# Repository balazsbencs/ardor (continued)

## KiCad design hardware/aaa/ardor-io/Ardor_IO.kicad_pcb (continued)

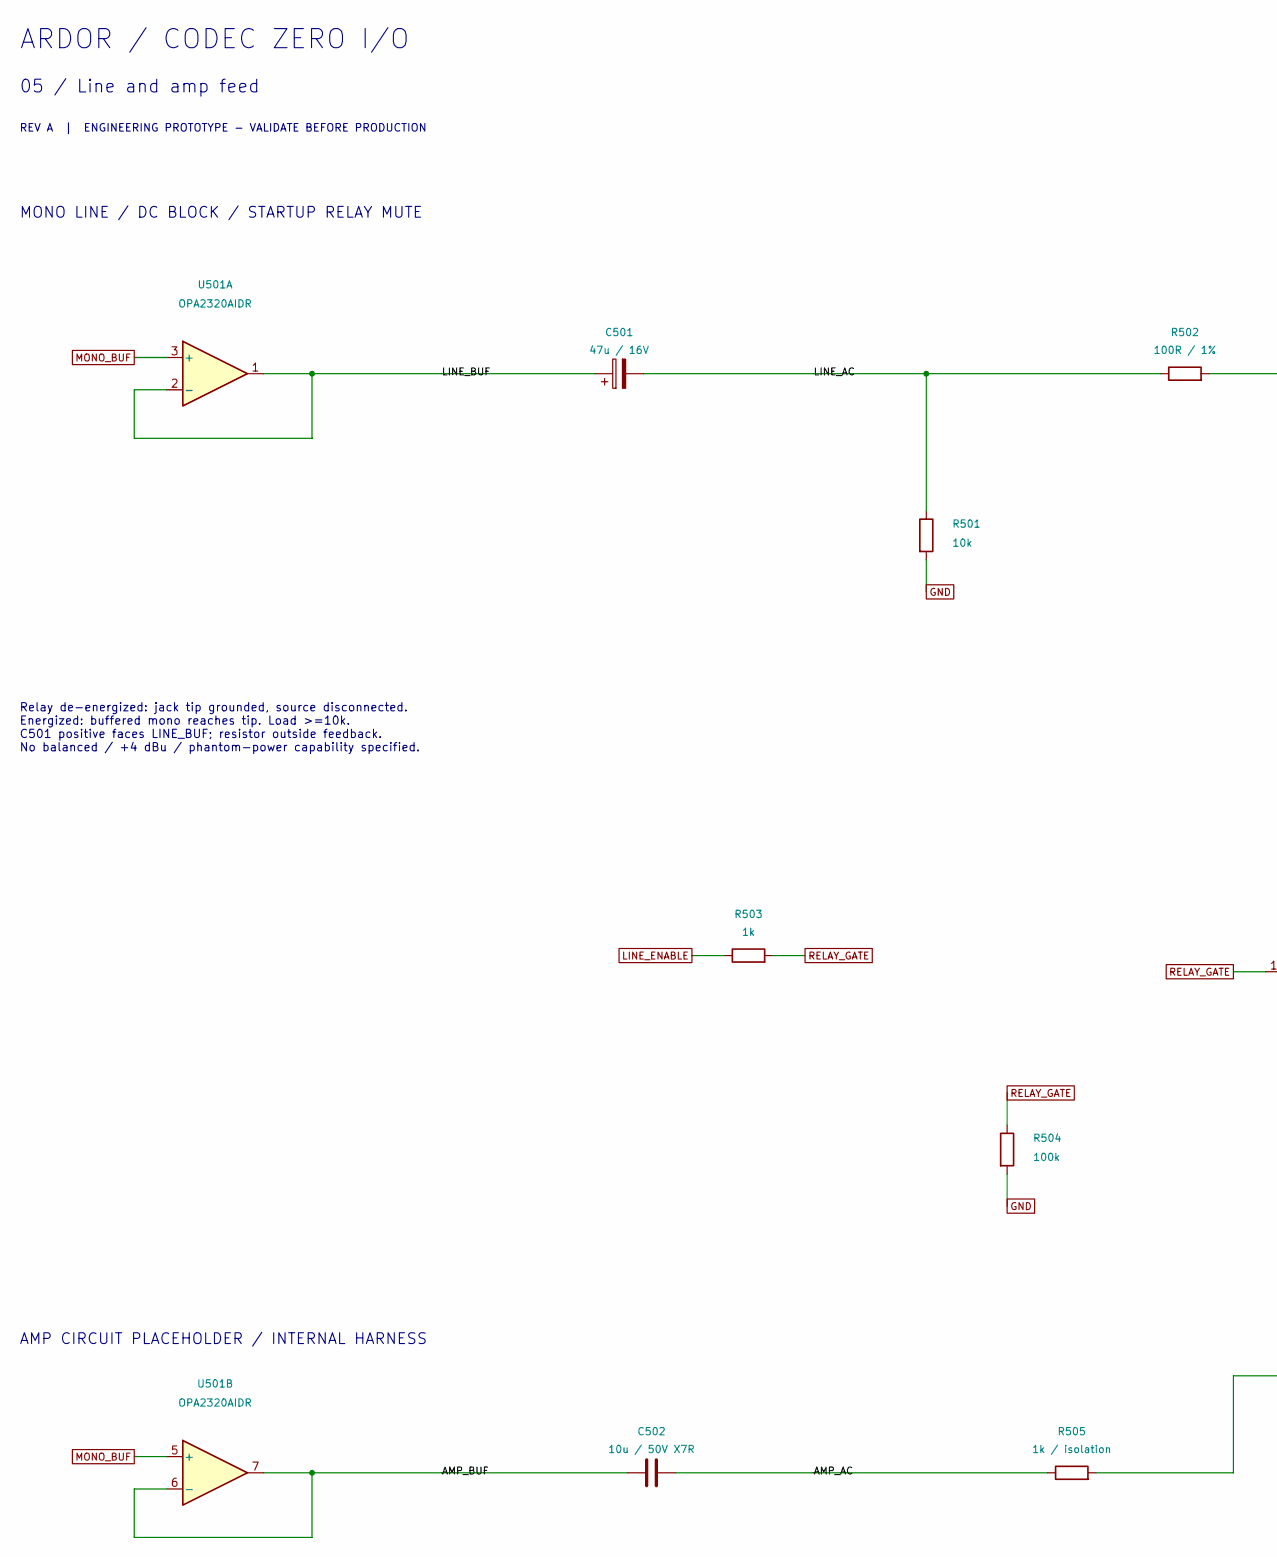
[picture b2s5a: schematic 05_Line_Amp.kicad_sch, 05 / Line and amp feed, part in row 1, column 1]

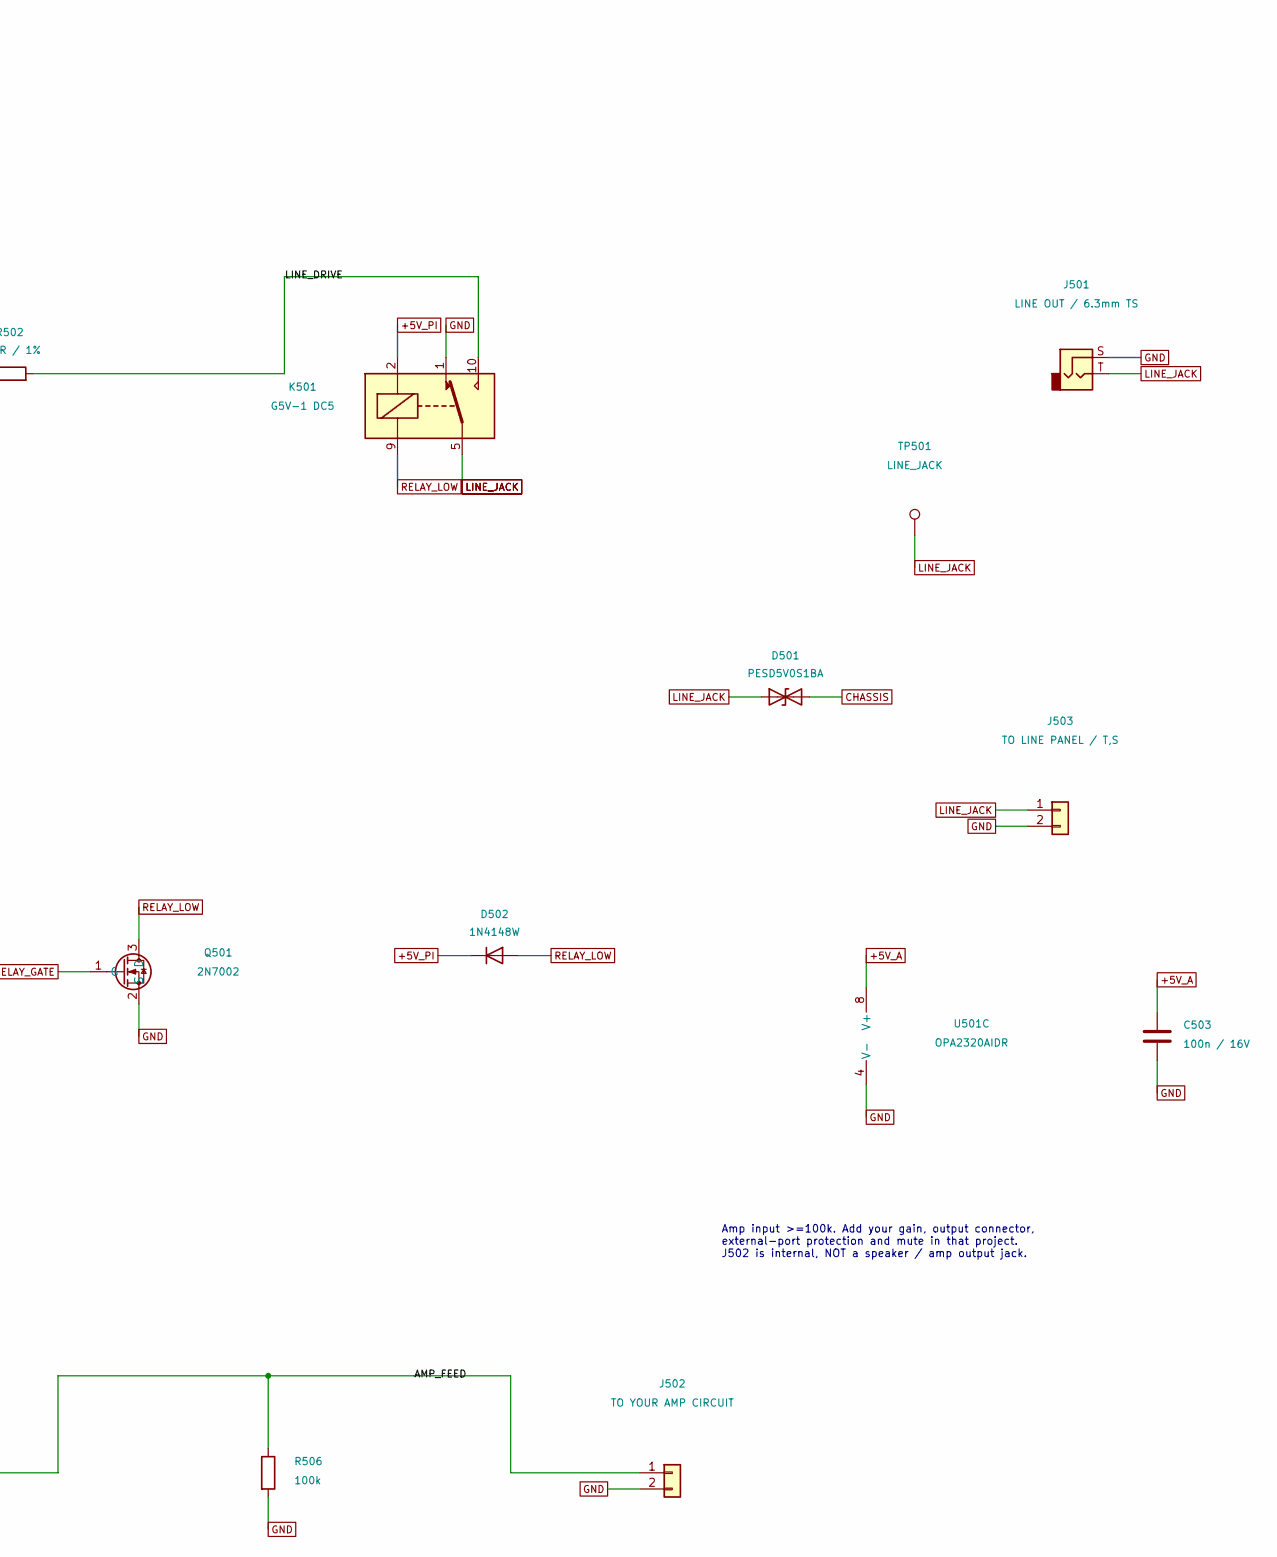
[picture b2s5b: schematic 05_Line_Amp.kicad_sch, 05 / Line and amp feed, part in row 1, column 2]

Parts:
C501: 47u / 16V; CP_Elec_6.3x5.4; MPN Panasonic EEE-FK1C470R
C502: 10u / 50V X7R; C_1206_3216Metric; MPN Samsung CL31B106KBHNNNE; JLCPCB Part # C89632
C503: 100n / 16V; C_0603_1608Metric
D501: PESD5V0S1BA; D_SOD-323; MPN Nexperia PESD5V0S1BA
D502: 1N4148W; D_SOD-123; MPN 1N4148W
J501: LINE OUT / 6.3mm TS
J502: TO YOUR AMP CIRCUIT; PinHeader_1x02_P2.54mm_Vertical
J503: TO LINE PANEL / T,S; PinHeader_1x02_P2.54mm_Vertical
K501: G5V-1 DC5; Relay_SPDT_Omron_G5V-1; MPN Omron G5V-1 DC5
Q501: 2N7002; SOT-23; MPN Nexperia 2N7002
R501: 10k; R_0603_1608Metric
R502: 100R / 1%; R_0603_1608Metric
R503: 1k; R_0603_1608Metric
R504, R506: 100k; R_0603_1608Metric
R505: 1k / isolation; R_0603_1608Metric
TP501: LINE_JACK; TestPoint_Pad_D1.5mm
U501: OPA2320AIDR; SOIC-8_3.9x4.9mm_P1.27mm; MPN TI OPA2320AIDR

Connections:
+5V_A: C503.1, U501.8 (V+); also elsewhere on the board
+5V_PI: D502.1 (K), K501.2; also elsewhere on the board
/05 / Line and amp feed/AMP_AC: C502.2, R505.1
/05 / Line and amp feed/AMP_BUF: C502.1, U501.6 (-), U501.7
/05 / Line and amp feed/AMP_FEED: J502.1, R505.2, R506.1
/05 / Line and amp feed/LINE_AC: C501.2, R501.1, R502.1
/05 / Line and amp feed/LINE_BUF: C501.1, U501.1, U501.2 (-)
/05 / Line and amp feed/LINE_DRIVE: K501.10, R502.2
CHASSIS: D501.2 (A2); also elsewhere on the board
GND: C503.2, J501.S, J502.2, J503.2, K501.1, Q501.2 (S), R501.2, R504.2, R506.2, U501.4 (V-); also elsewhere on the board
LINE_ENABLE: R503.1; also elsewhere on the board
LINE_JACK: D501.1 (A1), J501.T, J503.1, K501.5, K501.6, TP501.1
MONO_BUF: U501.3 (+), U501.5 (+); also elsewhere on the board
RELAY_GATE: Q501.1 (G), R503.2, R504.1
RELAY_LOW: D502.2 (A), K501.9, Q501.3 (D)

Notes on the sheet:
ARDOR / CODEC ZERO I/O
05 / Line and amp feed
REV A | ENGINEERING PROTOTYPE - VALIDATE BEFORE PRODUCTION
MONO LINE / DC BLOCK / STARTUP RELAY MUTE
Relay de-energized: jack tip grounded, source disconnected. Energized: buffered mono reaches tip. Load >=10k. C501 positive faces LINE_BUF; resistor outside feedback. No balanced / +4 dBu / phantom-power capability specified.
AMP CIRCUIT PLACEHOLDER / INTERNAL HARNESS
Amp input >=100k. Add your gain, output connector, external-port protection and mute in that project. J502 is internal, NOT a speaker / amp output jack.

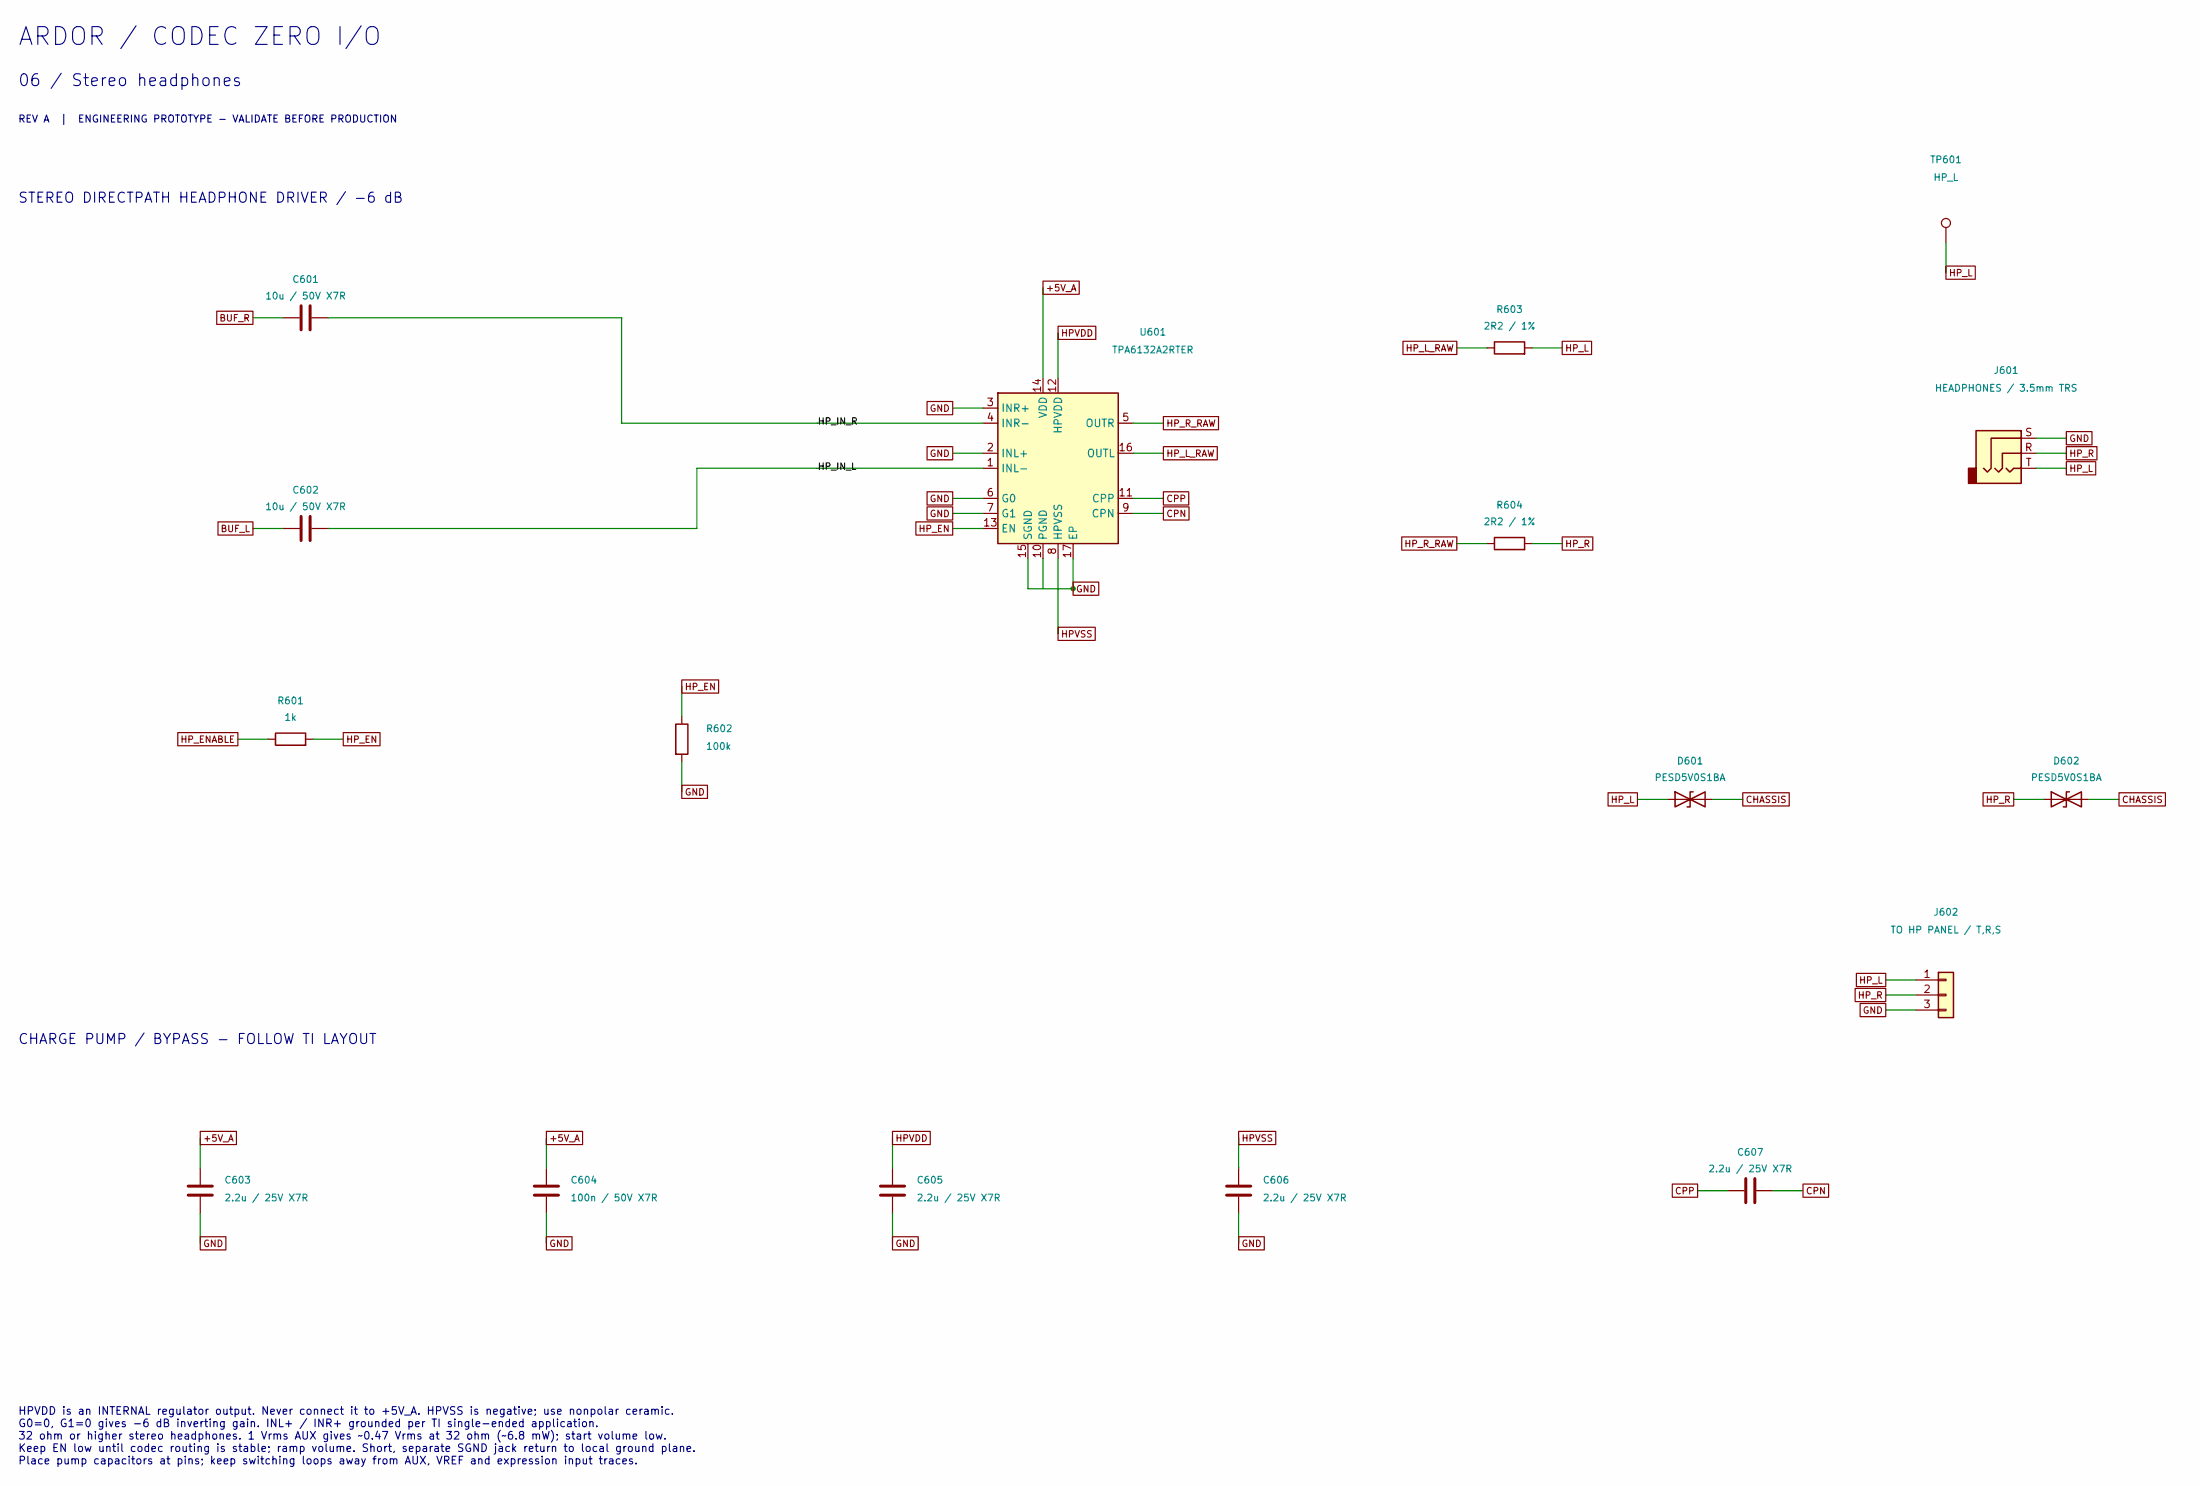
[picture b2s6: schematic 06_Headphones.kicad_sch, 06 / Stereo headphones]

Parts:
C601, C602: 10u / 50V X7R; C_1206_3216Metric; MPN Samsung CL31B106KBHNNNE; JLCPCB Part # C89632
C603, C605, C606, C607: 2.2u / 25V X7R; C_0805_2012Metric; MPN Samsung CL21B225KAFNNNE; JLCPCB Part # C19110
C604: 100n / 50V X7R; C_0603_1608Metric; MPN YAGEO CC0603KRX7R9BB104; JLCPCB Part # C14663
D601, D602: PESD5V0S1BA; D_SOD-323; MPN Nexperia PESD5V0S1BA,115; JLCPCB Part # C19224
J601: HEADPHONES / 3.5mm TRS
J602: TO HP PANEL / T,R,S; PinHeader_1x03_P2.54mm_Vertical
R601: 1k; R_0603_1608Metric; MPN UNI-ROYAL 0603WAF1001T5E; JLCPCB Part # C21190
R602: 100k; R_0603_1608Metric; MPN UNI-ROYAL 0603WAF1003T5E; JLCPCB Part # C25803
R603, R604: 2R2 / 1%; R_0603_1608Metric; MPN UNI-ROYAL 0603WAF220KT5E; JLCPCB Part # C22939
TP601: HP_L; TestPoint_Pad_D1.5mm
U601: TPA6132A2RTER; WQFN-16-1EP_3x3mm_P0.5mm_EP1.6x1.6mm_ThermalVias; MPN TI TPA6132A2RTER; JLCPCB Part # C69901

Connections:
+5V_A: C603.1, C604.1, U601.14 (VDD); also elsewhere on the board
/06 / Stereo headphones/HP_IN_L: C602.2, U601.1 (INL-)
/06 / Stereo headphones/HP_IN_R: C601.2, U601.4 (INR-)
BUF_L: C602.1; also elsewhere on the board
BUF_R: C601.1; also elsewhere on the board
CHASSIS: D601.2 (A2), D602.2 (A2); also elsewhere on the board
CPN: C607.2, U601.9 (CPN)
CPP: C607.1, U601.11 (CPP)
GND: C603.2, C604.2, C605.2, C606.2, J601.S, J602.3, R602.2, U601.2 (INL+), U601.3 (INR+), U601.6 (G0), U601.7 (G1), U601.10 (PGND), U601.15 (SGND), U601.17 (EP); also elsewhere on the board
HPVDD: C605.1, U601.12 (HPVDD)
HPVSS: C606.1, U601.8 (HPVSS)
HP_EN: R601.2, R602.1, U601.13 (EN)
HP_ENABLE: R601.1; also elsewhere on the board
HP_L: D601.1 (A1), J601.T, J602.1, R603.2, TP601.1
HP_L_RAW: R603.1, U601.16 (OUTL)
HP_R: D602.1 (A1), J601.R, J602.2, R604.2
HP_R_RAW: R604.1, U601.5 (OUTR)

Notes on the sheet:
ARDOR / CODEC ZERO I/O
06 / Stereo headphones
REV A | ENGINEERING PROTOTYPE - VALIDATE BEFORE PRODUCTION
STEREO DIRECTPATH HEADPHONE DRIVER / -6 dB
CHARGE PUMP / BYPASS - FOLLOW TI LAYOUT
HPVDD is an INTERNAL regulator output. Never connect it to +5V_A. HPVSS is negative; use nonpolar ceramic. G0=0, G1=0 gives -6 dB inverting gain. INL+ / INR+ grounded per TI single-ended application. 32 ohm or higher stereo headphones. 1 Vrms AUX gives ~0.47 Vrms at 32 ohm (~6.8 mW); start volume l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

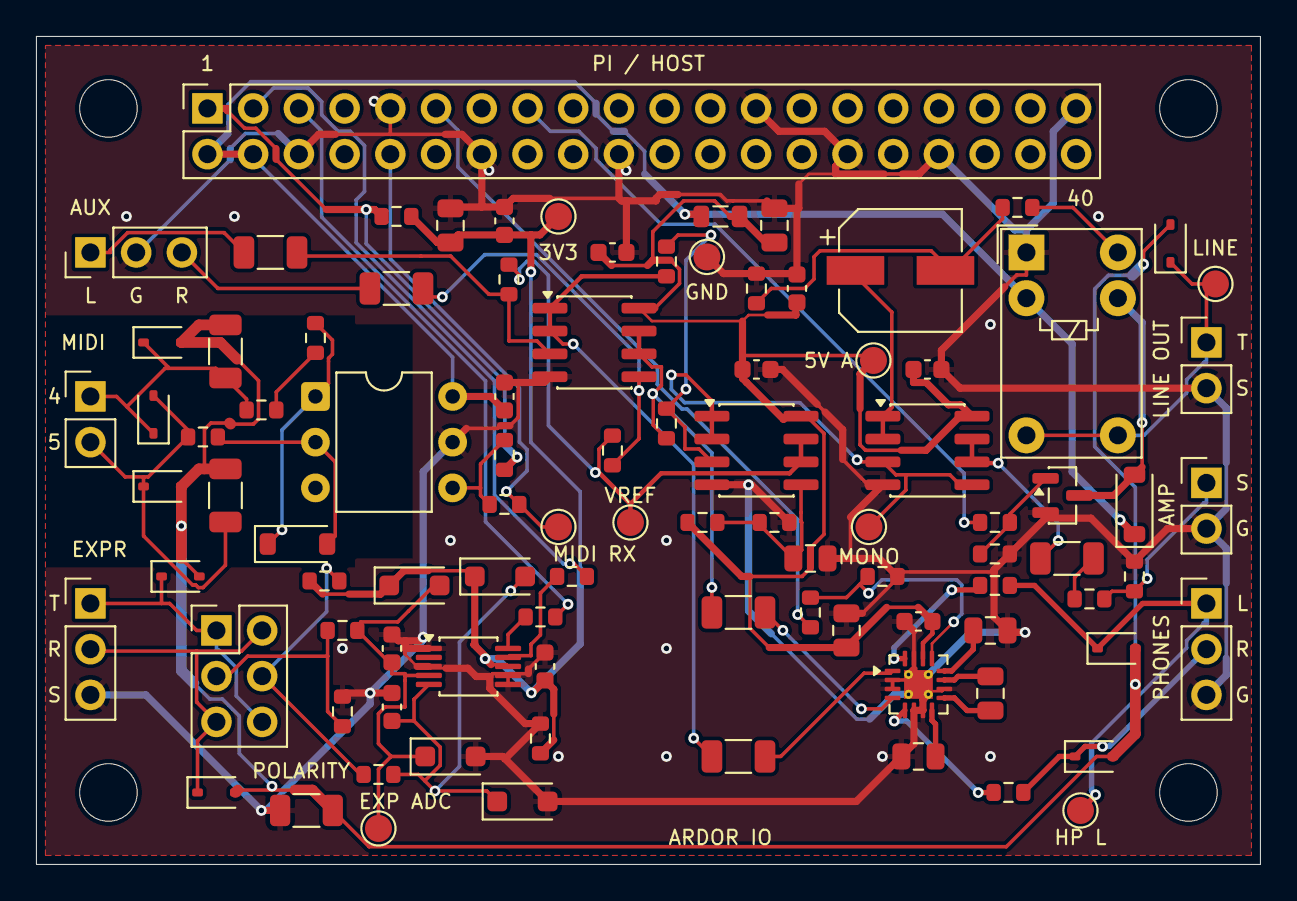
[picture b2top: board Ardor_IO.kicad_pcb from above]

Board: 2 copper layers, 68.0 x 46.0 mm, 99 parts (0 on the bottom side), 55 nets.

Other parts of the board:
H1, H2, H3, H4: M3 / PROVISIONAL; MountingHole_3.2mm_M3

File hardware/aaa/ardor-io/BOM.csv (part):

Reference,Value,MPN,Footprint,Datasheet,Assembly,Sheet,JLCPCB Part #
J101,PI 40-PIN HEADER,Samtec SSQ-120-03-G-D (verify stack height),Connector_PinSocket_2.54mm:PinSocket_2x20_P2.54mm_Vertical,,PCB,1,
J102,CODEC AUX L / GND / R,,Connector_PinHeader_2.54mm:PinHeader_1x03_P2.54mm_Vertical,,PCB,1,
FB101,600R @100MHz,Murata BLM21PG601SN1D,Inductor_SMD:L_0805_2012Metric,https://www.murata.com/products/productdata/8796738977822/EN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,PCB,1,C41556732
C101,22u / 10V X7R,Murata GRM21BZ71A226ME15L,Capacitor_SMD:C_0805_2012Metric,https://wmsc.lcsc.com/wmsc/upload/file/pdf/v2/lcsc/220124210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,PCB,1,C907991
C102,100n / 50V X7R,YAGEO CC0603KRX7R9BB104,Capacitor_SMD:C_0603_1608Metric,https://www.lcsc.com/datasheet/lcsc_datasheet_2211101700_YAG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,PCB,1,C14663
FB102,600R @100MHz,Murata BLM18AG601SN1D,Resistor_SMD:R_0603_1608Metric,https://www.lcsc.com/datasheet/lcsc_datasheet_2304140030_Mur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,PCB,1,C19330
C103,10u / 16V X7R,Samsung CL21B106KOQNNNE,Capacitor_SMD:C_0805_2012Metric,https://www.lcsc.com/datasheet/lcsc_datasheet_2304140030_Sam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,PCB,1,C95841
C104,100n / 50V X7R,YAGEO CC0603KRX7R9BB104,Capacitor_SMD:C_0603_1608Metric,https://www.lcsc.com/datasheet/lcsc_datasheet_2211101700_YAG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,PCB,1,C14663
R101,0R / chassis bond,UNI-ROYAL 1206W4F0000T5E,Resistor_SMD:R_1206_3216Metric,https://www.lcsc.com/datasheet/lcsc_datasheet_2206010200_UNI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,PCB,1,C17888
J201,MIDI IN - PANEL DIN,,,,Panel / wired,2,
FB201,600R @100MHz,Murata BLM18AG601SN1D,Resistor_SMD:R_0603_1608Metric,https://www.lcsc.com/datasheet/lcsc_datasheet_2304140030_Mur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,PCB,2,C19330
R201,220R / 1%,UNI-ROYAL 0603WAF2200T5E,Resistor_SMD:R_0603_1608Metric,https://www.lcsc.com/datasheet/lcsc_datasheet_2206010130_UNI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,PCB,2,C22962
FB202,600R @100MHz,Murata BLM18AG601SN1D,Resistor_SMD:R_0603_1608Metric,https://www.lcsc.com/datasheet/lcsc_datasheet_2304140030_Mur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,PCB,2,C19330
D201,1N4148W,ST(Semtech) 1N4148W,Diode_SMD:D_SOD-123,https://www.lcsc.com/datasheet/lcsc_datasheet_1811061725_ST-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,PCB,2,C81598
U201,H11L1M,onsemi H11L1M,Package_DIP:DIP-6_W7.62mm,https://www.onsemi.com/pdf/datasheet/h11l3m-d.pdf,PCB,2,
C201,100n / 50V X7R,YAGEO CC0603KRX7R9BB104,Capacitor_SMD:C_0603_1608Metric,https://www.lcsc.com/datasheet/lcsc_datasheet_2211101700_YAG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,PCB,2,C14663
R202,1k / 1%,UNI-ROYAL 0603WAF1001T5E,Resistor_SMD:R_0603_1608Metric,https://www.lcsc.com/datasheet/lcsc_datasheet_2206010130_UNI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,PCB,2,C21190
R203,100R,UNI-ROYAL 0603WAF1000T5E,Resistor_SMD:R_0603_1608Metric,https://www.lcsc.com/datasheet/lcsc_datasheet_2411221126_UNI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,PCB,2,C22775
D202,PESD5V0S1BA,"Nexperia PESD5V0S1BA,115",Diode_SMD:D_SOD-323,https://assets.nexperia.com/documents/data-sheet/PESD5V0S1BA.pdf,PCB,2,C19224
C202,100p / 1kV C0G,CCTC TCC1206COG101J102DT,Capacitor_SMD:C_1206_3216Metric,https://wmsc.lcsc.com/wmsc/upload/file/pdf/v2/lcsc/230414003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,PCB,2,C367316
C203,100p / 1kV C0G,CCTC TCC1206COG101J102DT,Capacitor_SMD:C_1206_3216Metric,https://wmsc.lcsc.com/wmsc/upload/file/pdf/v2/lcsc/230414003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,PCB,2,C367316
D203,PESD24VL1BA,"Nexperia PESD24VL1BA,115",Diode_SMD:D_SOD-323,https://assets.nexperia.com/documents/data-sheet/PESD24VL1BA.pdf,PCB,2,C69324
D204,PESD24VL1BA,"Nexperia PESD24VL1BA,115",Diode_SMD:D_SOD-323,https://assets.nexperia.com/documents/data-sheet/PESD24VL1BA.pdf,PCB,2,C69324
J301,EXPRESSION / 6.3mm TRS,,,,Panel / wired,3,
JP301,POLARITY / 2 SHUNTS,,Connector_PinHeader_2.54mm:PinHeader_2x03_P2.54mm_Vertical,,PCB,3,
R301,1k / 1%,UNI-ROYAL 0603WAF1001T5E,Resistor_SMD:R_0603_1608Metric,https://www.lcsc.com/datasheet/lcsc_datasheet_2206010130_UNI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,PCB,3,C21190
R302,10k / 1%,UNI-ROYAL 0603WAF1002T5E,Resistor_SMD:R_0603_1608Metric,https://www.lcsc.com/datasheet/lcsc_datasheet_2206010045_UNI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,PCB,3,C25804
R303,1M,UNI-ROYAL 0603WAF1004T5E,Resistor_SMD:R_0603_1608Metric,https://www.lcsc.com/datasheet/lcsc_datasheet_2206010130_UNI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,PCB,3,C22935
C301,100n / 50V X7R,YAGEO CC0603KRX7R9BB104,Capacitor_SMD:C_0603_1608Metric,https://www.lcsc.com/datasheet/lcsc_datasheet_2211101700_YAG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,PCB,3,C14663
D303,BAT54H,"Nexperia BAT54H,115",Diode_SMD:D_SOD-123F,https://www.lcsc.com/datasheet/lcsc_datasheet_2407241029_Nex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,PCB,3,C426769
D304,BAT54H,"Nexperia BAT54H,115",Diode_SMD:D_SOD-123F,https://www.lcsc.com/datasheet/lcsc_datasheet_2407241029_Nex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,PCB,3,C426769
D301,PESD5V0S1BA,"Nexperia PESD5V0S1BA,115",Diode_SMD:D_SOD-323,https://assets.nexperia.com/documents/data-sheet/PESD5V0S1BA.pdf,PCB,3,C19224
D302,PESD5V0S1BA,"Nexperia PESD5V0S1BA,115",Diode_SMD:D_SOD-323,https://assets.nexperia.com/documents/data-sheet/PESD5V0S1BA.pdf,PCB,3,C19224
U301,ADS1115IDGS,TI ADS1115IDGSR,Package_SO:VSSOP-10_3x3mm_P0.5mm,https://www.ti.com/lit/ds/symlink/ads1115.pdf,PCB,3,C37593
R304,10k / 1%,UNI-ROYAL 0603WAF1002T5E,Resistor_SMD:R_0603_1608Metric,https://www.lcsc.com/datasheet/lcsc_datasheet_2206010045_UNI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,PCB,3,C25804
C302,100n / 50V X7R,YAGEO CC0603KRX7R9BB104,Capacitor_SMD:C_0603_1608Metric,https://www.lcsc.com/datasheet/lcsc_datasheet_2211101700_YAG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,PCB,3,C14663
C303,100n / 50V X7R,YAGEO CC0603KRX7R9BB104,Capacitor_SMD:C_0603_1608Metric,https://www.lcsc.com/datasheet/lcsc_datasheet_2211101700_YAG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,PCB,3,C14663
R305,33R,UNI-ROYAL 0603WAF330JT5E,Resistor_SMD:R_0603_1608Metric,https://www.lcsc.com/datasheet/lcsc_datasheet_2206010116_UNI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,PCB,3,C23140
R306,33R,UNI-ROYAL 0603WAF330JT5E,Resistor_SMD:R_0603_1608Metric,https://www.lcsc.com/datasheet/lcsc_datasheet_2206010116_UNI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,PCB,3,C23140
R307,2.2k / rail bleed,UNI-ROYAL 0603WAF2201T5E,Resistor_SMD:R_0603_1608Metric,https://www.lcsc.com/datasheet/lcsc_datasheet_2206010230_UNI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,PCB,3,C4190
D305,BAT54H,"Nexperia BAT54H,115",Diode_SMD:D_SOD-123F,https://www.lcsc.com/datasheet/lcsc_datasheet_2407241029_Nex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,PCB,3,C426769
D306,BAT54H,"Nexperia BAT54H,115",Diode_SMD:D_SOD-123F,https://www.lcsc.com/datasheet/lcsc_datasheet_2407241029_Nex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,PCB,3,C426769
C401,10u / 50V X7R,Samsung CL31B106KBHNNNE,Capacitor_SMD:C_1206_3216Metric,https://media.digikey.com/pdf/Data%20Sheets/Samsung%20PDFs/C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,PCB,4,C89632
R401,100k / 1%,UNI-ROYAL 0603WAF1003T5E,Resistor_SMD:R_0603_1608Metric,https://www.lcsc.com/datasheet/lcsc_datasheet_2206010045_UNI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,PCB,4,C25803
U401,OPA2320AIDR,TI OPA2320AIDR,Package_SO:SOIC-8_3.9x4.9mm_P1.27mm,https://www.ti.com/lit/ds/symlink/opa2320.pdf,PCB,4,C2863402
R403,10k / 0.1%,YAGEO RT0603BRD0710KL,Resistor_SMD:R_0603_1608Metric,https://wmsc.lcsc.com/wmsc/upload/file/pdf/v2/lcsc/181108211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,PCB,4,C95204
C402,10u / 50V X7R,Samsung CL31B106KBHNNNE,Capacitor_SMD:C_1206_3216Metric,https://media.digikey.com/pdf/Data%20Sheets/Samsung%20PDFs/C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,PCB,4,C89632
R402,100k / 1%,UNI-ROYAL 0603WAF1003T5E,Resistor_SMD:R_0603_1608Metric,https://www.lcsc.com/datasheet/lcsc_datasheet_2206010045_UNI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,PCB,4,C25803
R404,10k / 0.1%,YAGEO RT0603BRD0710KL,Resistor_SMD:R_0603_1608Metric,https://wmsc.lcsc.com/wmsc/upload/file/pdf/v2/lcsc/181108211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,PCB,4,C95204
U402,OPA2320AIDR,TI OPA2320AIDR,Package_SO:SOIC-8_3.9x4.9mm_P1.27mm,https://www.ti.com/lit/ds/symlink/opa2320.pdf,PCB,4,C2863402
R405,10k / 1%,UNI-ROYAL 0603WAF1002T5E,Resistor_SMD:R_0603_1608Metric,https://www.lcsc.com/datasheet/lcsc_datasheet_2206010045_UNI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,PCB,4,C25804
R406,10k / 1%,UNI-ROYAL 0603WAF1002T5E,Resistor_SMD:R_0603_1608Metric,https://www.lcsc.com/datasheet/lcsc_datasheet_2206010045_UNI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,PCB,4,C25804
C403,10u / 16V X7R,Samsung CL21B106KOQNNNE,Capacitor_SMD:C_0805_2012Metric,https://www.lcsc.com/datasheet/lcsc_datasheet_2304140030_Sam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,PCB,4,C95841
C404,100n / 50V X7R,YAGEO CC0603KRX7R9BB104,Capacitor_SMD:C_0603_1608Metric,https://www.lcsc.com/datasheet/lcsc_datasheet_2211101700_YAG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,PCB,4,C14663
C405,100n / 50V X7R,YAGEO CC0603KRX7R9BB104,Capacitor_SMD:C_0603_1608Metric,https://www.lcsc.com/datasheet/lcsc_datasheet_2211101700_YAG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,PCB,4,C14663
U501,OPA2320AIDR,TI OPA2320AIDR,Package_SO:SOIC-8_3.9x4.9mm_P1.27mm,https://www.ti.com/lit/ds/symlink/opa2320.pdf,PCB,5,C2863402
C501,47u / 16V,Panasonic EEEFK1C470P,Ardor_Capacitor:CP_Elec_Panasonic_FK_D6.3_H5.8,https://industrial.panasonic.com/cdbs/www-data/pdf/RDE0000/A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,PCB,5,C336261
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
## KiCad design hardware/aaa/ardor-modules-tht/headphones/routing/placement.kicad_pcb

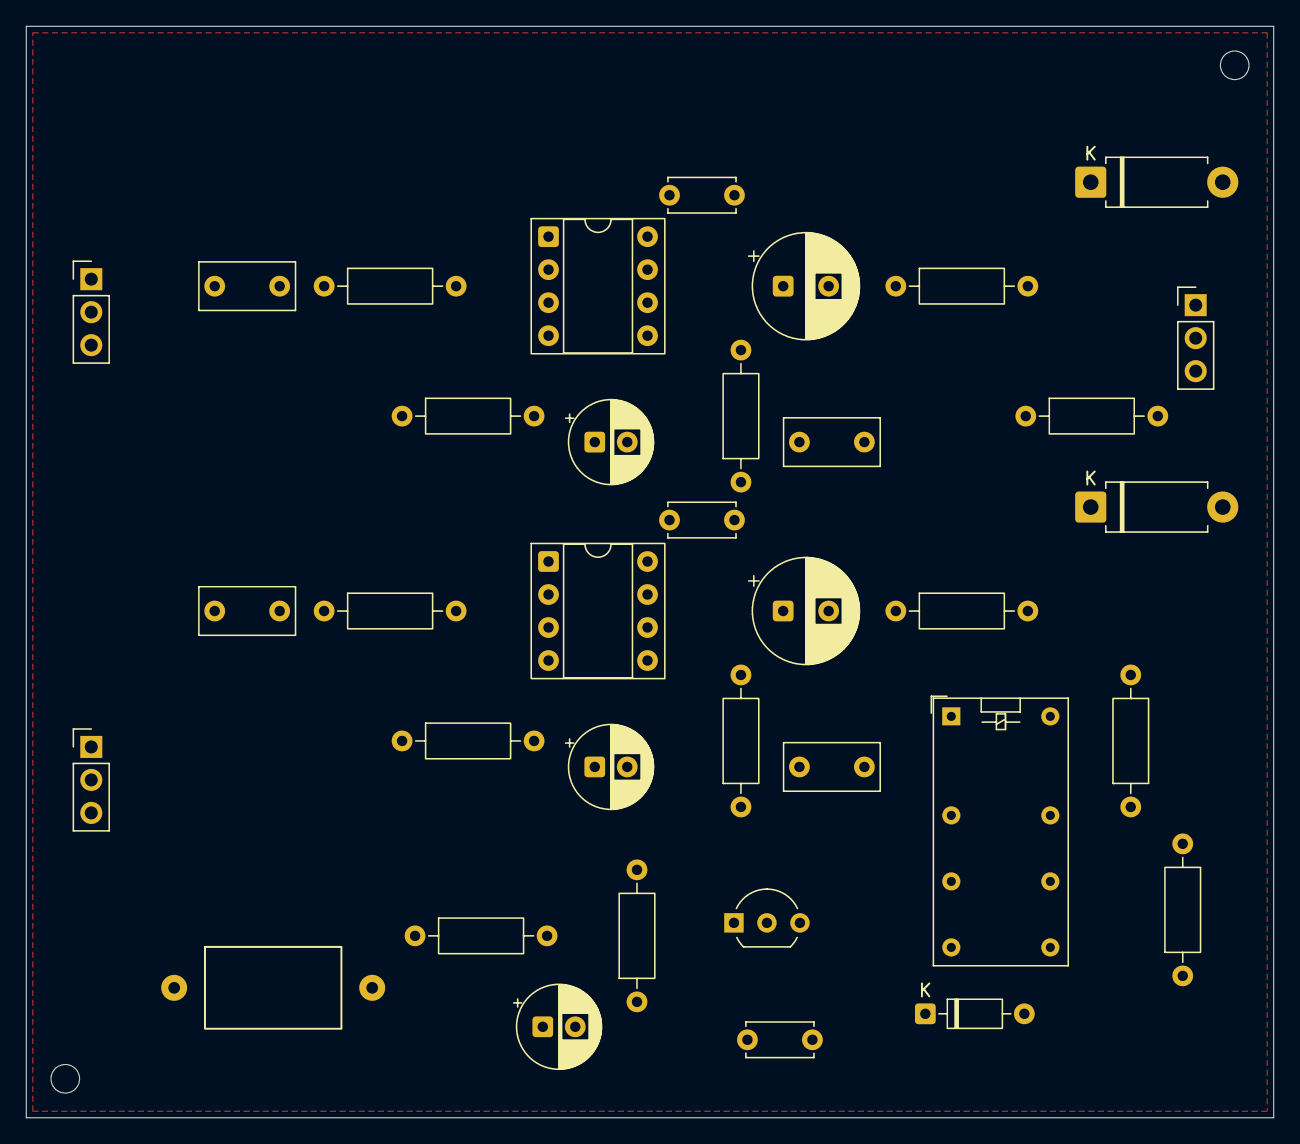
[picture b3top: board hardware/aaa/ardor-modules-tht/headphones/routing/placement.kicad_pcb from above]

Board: 2 copper layers, 96.0 x 84.0 mm, 38 parts (0 on the bottom side), 25 nets, no tracks yet.

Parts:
C101: 100u / 25V; CP_Radial_D6.3mm_P2.50mm
C102, C641, C642: 100n / 50V X7R; C_Disc_D5.0mm_W2.5mm_P5.00mm
C601, C602: 1u / 63V FILM; C_Rect_L7.2mm_W3.5mm_P5.00mm_FKS2_FKP2_MKS2_MKP2
C631, C632: 10u / 25V; CP_Radial_D6.3mm_P2.50mm
C651, C652: 470u / 16V; CP_Radial_D8.0mm_P3.50mm
C661, C662: 47n / 50V FILM; C_Rect_L7.2mm_W3.5mm_P5.00mm_FKS2_FKP2_MKS2_MKP2
D601, D602: SA5.0CA-E3/54; D_DO-15_P10.16mm_Horizontal
D603: 1N4148; D_DO-35_SOD27_P7.62mm_Horizontal
FB101: 800R@100MHz / WE 7427501; Ferrite_WE_7427501_P15.24mm
H1, H2: MountingHole_2.2mm_M2
J101: 5V POWER + ENABLE INPUT; PinHeader_1x03_P2.54mm_Vertical
J102: STEREO AUDIO INPUT FROM SOURCE; PinHeader_1x03_P2.54mm_Vertical
J602: STEREO HEADPHONE AUDIO OUTPUT; PinHeader_1x03_P2.54mm_Vertical
K601: G5V-2-H1 DC5; Relay_DPDT_Omron_G5V-2
Q601: 2N3904 / E-B-C; TO-92_Inline_Wide
R101: 0R / WIRE LINK; R_Axial_DIN0207_L6.3mm_D2.5mm_P10.16mm_Horizontal
R601: 470R / 1% 0.25W; R_Axial_DIN0207_L6.3mm_D2.5mm_P10.16mm_Horizontal
R602: 100k / 1% 0.25W; R_Axial_DIN0207_L6.3mm_D2.5mm_P10.16mm_Horizontal
R611, R612: 39k / 1% 0.25W; R_Axial_DIN0207_L6.3mm_D2.5mm_P10.16mm_Horizontal
R621, R622, R641, R642: 1k / 1% 0.25W; R_Axial_DIN0207_L6.3mm_D2.5mm_P10.16mm_Horizontal
R631, R632: 2.2R / 1% 0.25W; R_Axial_DIN0207_L6.3mm_D2.5mm_P10.16mm_Horizontal
R651, R652: 10R / 1% 0.25W; R_Axial_DIN0207_L6.3mm_D2.5mm_P10.16mm_Horizontal
U601, U602: LM386N-1/NOPB; DIP-8_W7.62mm_Socket

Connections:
/+5V: D603.1, FB101.1, J101.1, K601.1
/+5V_A: C101.1, C102.1, C641.1, C642.1, FB101.2, U601.6, U602.6
/CHASSIS: D601.2, D602.2, R101.1
/DRIVE_L: K601.8, R631.2, R641.1
/DRIVE_R: K601.9, R632.2, R642.1
/GND: C101.2, C102.2, C631.2, C632.2, C641.2, C642.2, C661.2, C662.2, J101.2, J102.2, J602.3, K601.6, K601.11, Q601.1, R101.2, R602.2, R621.2, R622.2, R641.2, R642.2, U601.2, U601.4, U602.2, U602.4
/HP_L: D601.1, J602.1, K601.4
/HP_R: D602.1, J602.2, K601.13
/RELAY_LOW: D603.2, K601.16, Q601.3
unnamed: C601.2, R611.1
unnamed: C602.2, R612.1
unnamed: C651.1, R651.1, U601.5
unnamed: C651.2, R631.1
unnamed: C652.1, R652.1, U602.5
unnamed: C652.2, R632.1
unnamed: C661.1, R651.2
unnamed: C662.1, R652.2
unnamed: J101.3, R601.1
unnamed: C601.1, J102.1
unnamed: C602.1, J102.3
unnamed: Q601.2, R601.2, R602.1
unnamed: R611.2, R621.1, U601.3
unnamed: C631.1, U601.7
unnamed: R612.2, R622.1, U602.3
unnamed: C632.1, U602.7

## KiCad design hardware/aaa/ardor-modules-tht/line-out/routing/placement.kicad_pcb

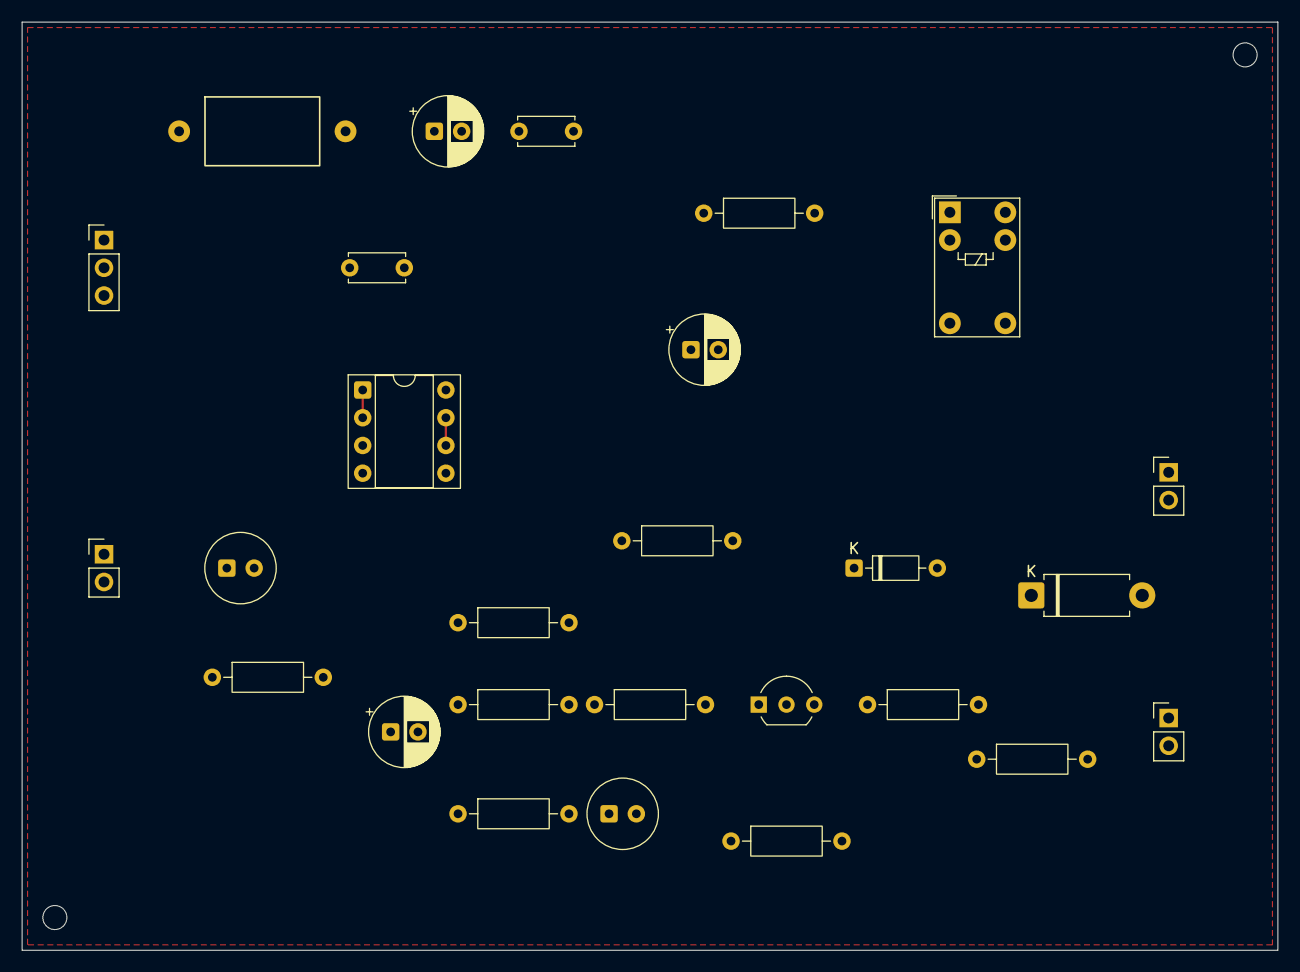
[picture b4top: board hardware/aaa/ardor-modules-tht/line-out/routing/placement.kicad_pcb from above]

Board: 2 copper layers, 115.0 x 85.0 mm, 29 parts (0 on the bottom side), 17 nets.

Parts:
C101: 22u / 25V polarized; CP_Radial_D6.3mm_P2.50mm
C102, C404: 100n / 50V X7R; C_Disc_D5.0mm_W2.5mm_P5.00mm
C401, C502: 10u / 25V BIPOLAR; CP_Bipolar_D6.3mm_P2.50mm
C403: 10u / 25V polarized; CP_Radial_D6.3mm_P2.50mm
C501: 47u / 25V polarized; CP_Radial_D6.3mm_P2.50mm
D501: SA5.0CA-E3/54; D_DO-15_P10.16mm_Horizontal
D502: 1N4148; D_DO-35_SOD27_P7.62mm_Horizontal
FB101: 800R@100MHz / WE 7427501; Ferrite_WE_7427501_P15.24mm
H1, H2: MountingHole_2.2mm_M2
J101: 5V POWER + ENABLE INPUT; PinHeader_1x03_P2.54mm_Vertical
J102: MONO AUDIO INPUT FROM SOURCE; PinHeader_1x02_P2.54mm_Vertical
J502: AUDIO OUTPUT TO AMP INPUT; PinHeader_1x02_P2.54mm_Vertical
J503: LINE AUDIO OUTPUT TO TS SOCKET; PinHeader_1x02_P2.54mm_Vertical
K501: Omron G5V-1 DC5; Relay_SPDT_Omron_G5V-1
Q501: 2N3904 / E-B-C; TO-92_Inline_Wide
R101: 0R / 1% 0.25W; R_Axial_DIN0207_L6.3mm_D2.5mm_P10.16mm_Horizontal
R401, R504, R506: 100kR / 1% 0.25W; R_Axial_DIN0207_L6.3mm_D2.5mm_P10.16mm_Horizontal
R405, R406, R501: 10kR / 1% 0.25W; R_Axial_DIN0207_L6.3mm_D2.5mm_P10.16mm_Horizontal
R502: 100R / 1% 0.25W; R_Axial_DIN0207_L6.3mm_D2.5mm_P10.16mm_Horizontal
R503: 470R / 1% 0.25W; R_Axial_DIN0207_L6.3mm_D2.5mm_P10.16mm_Horizontal
R505: 1kR / 1% 0.25W; R_Axial_DIN0207_L6.3mm_D2.5mm_P10.16mm_Horizontal
U501: MCP6022-I/P; DIP-8_W7.62mm_Socket

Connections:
/+5V: D502.1, FB101.1, J101.1, K501.2
/+5V_A: C101.1, C102.1, C404.1, FB101.2, R405.1, U501.8
/CHASSIS: D501.2, R101.1
/GND: C101.2, C102.2, C403.2, C404.2, J101.2, J102.2, J502.2, J503.2, K501.1, Q501.1, R101.2, R406.2, R501.2, R504.2, R506.2, U501.4
/VREF: R401.2, U501.6, U501.7
unnamed: C501.2, R501.1, R502.1
unnamed: C502.2, R505.1
unnamed: D501.1, J503.1, K501.5, K501.6
unnamed: D502.2, K501.9, Q501.3
unnamed: J101.3, R503.1
unnamed: C401.1, J102.1
unnamed: J502.1, R505.2, R506.1
unnamed: K501.10, R502.2
unnamed: Q501.2, R503.2, R504.1
unnamed: C401.2, R401.1, U501.3
unnamed: C501.1, C502.1, U501.1, U501.2
unnamed: C403.1, R405.2, R406.1, U501.5
